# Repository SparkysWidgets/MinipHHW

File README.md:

Welcome To: MinipH Hardware Repo!!
================================

##### Note: This is for the MinipH Hardware Version 4 Branch

MinipH Hardware Design Files in EAGLE. Not much to say, there are some custom parts will add Library after I clean it up!

Schematic Info
-------------------------
##### Basic schematic is split into sections
- Analog Front End - pH gain and offset stages
- 12bit ADC
- VREF
- VGND generated by Op-amp, probe is biased
- Reverse V protection pFET

Board Layout Info
-------------------------
##### Form factor is consistent with all other mini interface boards

- Standard 2.54mm pitch header and Grove style connector
- Guard ring on pH input stage, care must be taken in layout here
- Added back in solder bridge jumper to select if Vref should be used or not (Its an expensive BurrBrown guy and really only needed for super sensitive use)

Errata
-------------------------

##### Just a quick list of current issues
- Mostly stable design older errata resolved, new may be created will be updated

Firmware
-------------------------

- Take a look in [MinipH's Firmware Repo](https://github.com/SparkysWidgets/MinipHBFW) For Arduino!
- Check out my USB pH interface[LeoPhi](https://www.sparkyswidgets.com/portfolio-item/leophi-usb-arduino-ph-sensor/) for a powerful and easy to use USB PH Probe interface!

Basic Usage
-------------------------

####See [MinipH's Firmware Repo](https://github.com/SparkysWidgets/MinipHBFW)

License Info
-------------------------

<p>This is a fully open source project released under the CC BY license</p>
<br />
<span xmlns:dct="http://purl.org/dc/terms/" property="dct:title">MinipH</span> by <a xmlns:cc="http://creativecommons.org/ns#" href="www.sparkyswidgets.com" property="cc:attributionName" rel="cc:attributionURL">Ryan Edwards, Sparky's Widgets</a> is licensed under a <a rel="license" href="http://creativecommons.org/licenses/by-sa/3.0/deed.en_US">Creative Commons Attribution-ShareAlike 3.0 Unported License</a>.<br />
Based on a work at <a xmlns:dct="http://purl.org/dc/terms/" href="/portfolio-item/leophi-usb-arduino-ph-sensor/" rel="dct:source">http://www.sparkyswidgets.com/portfolio-item/miniph-i2c-ph-interface/</a>

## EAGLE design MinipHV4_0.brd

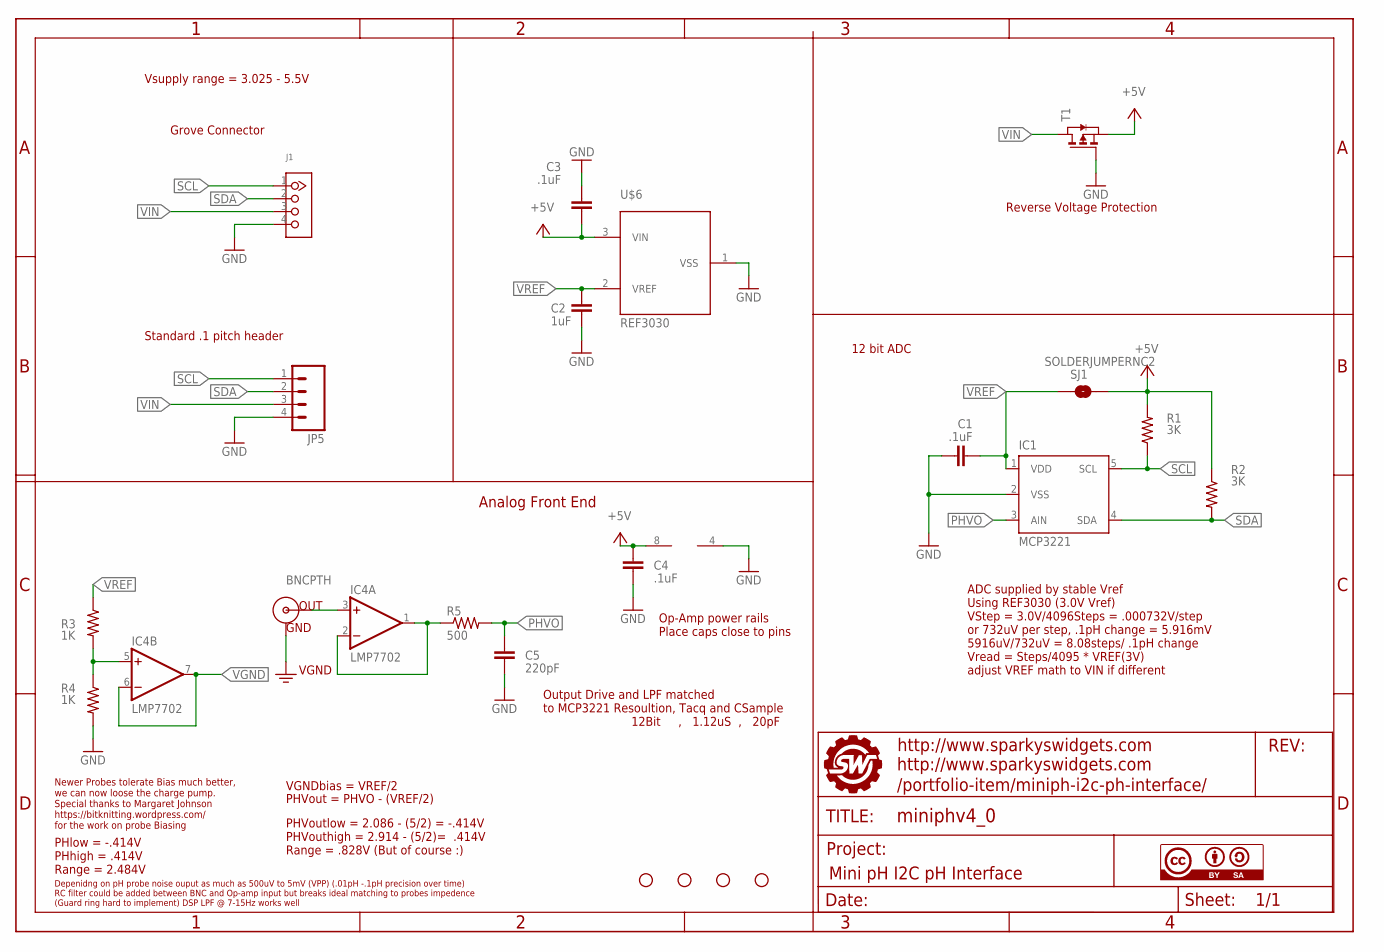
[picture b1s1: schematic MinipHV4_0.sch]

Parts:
C1, C3, C4: .1uF; 0805
C2: 1uF; 0805
C5: 220pF; 0805
IC1: MCP3221; SOT23-DBV
IC4: LMP7702; SO08
J1: TWIG-4P-2.0-2.0; 4P-2.0
JP1, JP2, JP3, JP4: STAND-OFF
JP5: M04PTH; 1X04
R1, R2: 3K; 0805
R3, R4: 1K; 0805
R5: 500; 0805
SJ1: SOLDERJUMPERNC2; SJ_2S-NOTRACE
T1: PMOSSOT23; SOT-23
U$2: BNCPTH; BNC
U$4: FRAME_MINIPH; SWPCBLOGOWITHINFO
U$5: CC-BY-SA
U$6: REF3030; SOT-23

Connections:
+5V: C3.1, C4.1, IC4.8 (V+), R1.2, R2.1, SJ1.2, T1.2 (S), U$6.3 (VIN)
GND: C1.1, C2.2, C3.2, C4.2, C5.2, IC1.2 (VSS), IC4.4 (V-), J1.4, JP5.4, R4.2, T1.3 (G), U$6.1 (VSS)
unnamed: IC4.5 (+IN), R3.2, R4.1
unnamed: IC4.1 (OUT), IC4.2 (-IN), R5.1
PHVIN: IC4.3 (+IN), U$2.S (OUT)
PHVO: C5.1, IC1.3 (AIN), R5.2
SCL: IC1.5 (SCL), J1.1, JP5.1, R1.1
SDA: IC1.4 (SDA), J1.2, JP5.2, R2.2
VGND: IC4.6 (-IN), IC4.7 (OUT), U$2.GND
VIN: J1.3, JP5.3, T1.1 (D)
VREF: C1.2, C2.1, IC1.1 (VDD), R3.1, SJ1.1, U$6.2 (VREF)

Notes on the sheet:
Grove Connector
Standard .1 pitch header
12 bit ADC
Analog Front End
Op-Amp power rails Place caps close to pins
Depenidng on pH probe noise ouput as much as 500uV to 5mV (VPP) (.01pH -.1pH precision over time) RC filter could be added between BNC and Op-amp input but breaks ideal matching to probes impedence (Guard ring hard to implement) DSP LPF @ 7-15Hz works well
Newer Probes tolerate Bias much better, we can now loose the charge pump. Special thanks to Margaret Johnson https://bitknitting.wordpress.com/ for the work on probe Biasing
VGNDbias = VREF/2
PHVout = PHVO - (VREF/2)
PHlow = -.414V PHhigh = .414V Range = 2.484V
PHVoutlow = 2.086 - (5/2) = -.414V PHVouthigh = 2.914 - (5/2)= .414V Range = .828V (But of course :)
Output Drive and LPF matched to MCP3221 Resoultion, Tacq and CSample 12Bit , 1.12uS , 20pF
Vsupply range = 3.025 - 5.5V
ADC supplied by stable Vref Using REF3030 (3.0V Vref) VStep = 3.0V/4096Steps = .000732V/step or 732uV per step, .1pH change = 5.916mV 5916uV/732uV = 8.08steps/ .1pH change Vread = Steps/4095 * VREF(3V) adjust VREF math to VIN if different
Reverse Voltage Protection

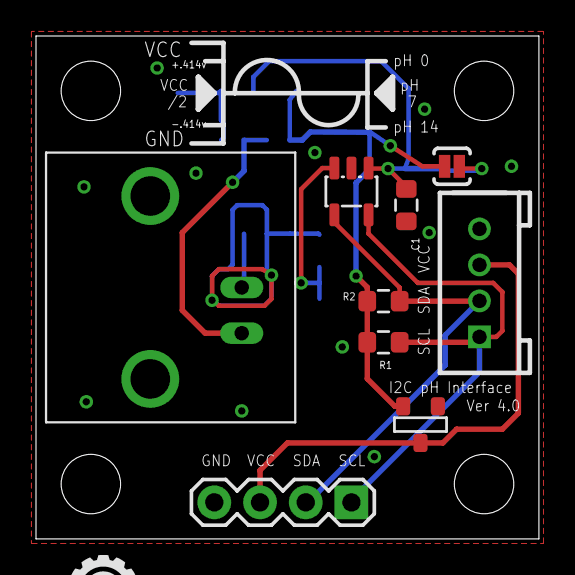
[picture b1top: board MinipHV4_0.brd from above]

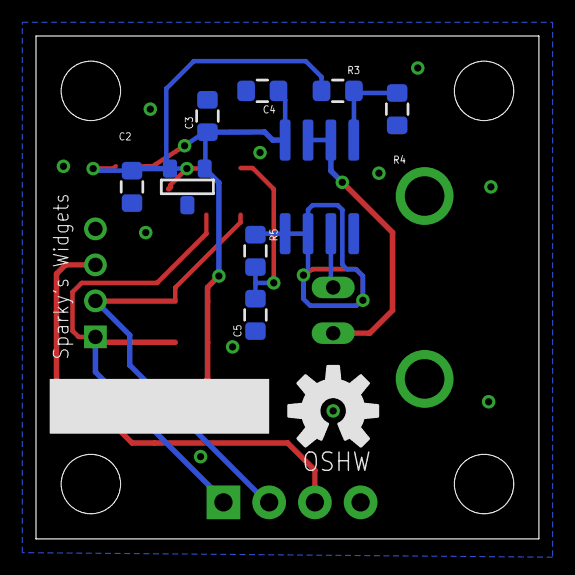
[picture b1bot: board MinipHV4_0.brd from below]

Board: 2 copper layers, 27.9 x 27.9 mm, 27 parts (10 on the bottom side), 11 nets.

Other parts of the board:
U$1, U$7: SILK_ARROW
U$3: OSHW-LOGO-M

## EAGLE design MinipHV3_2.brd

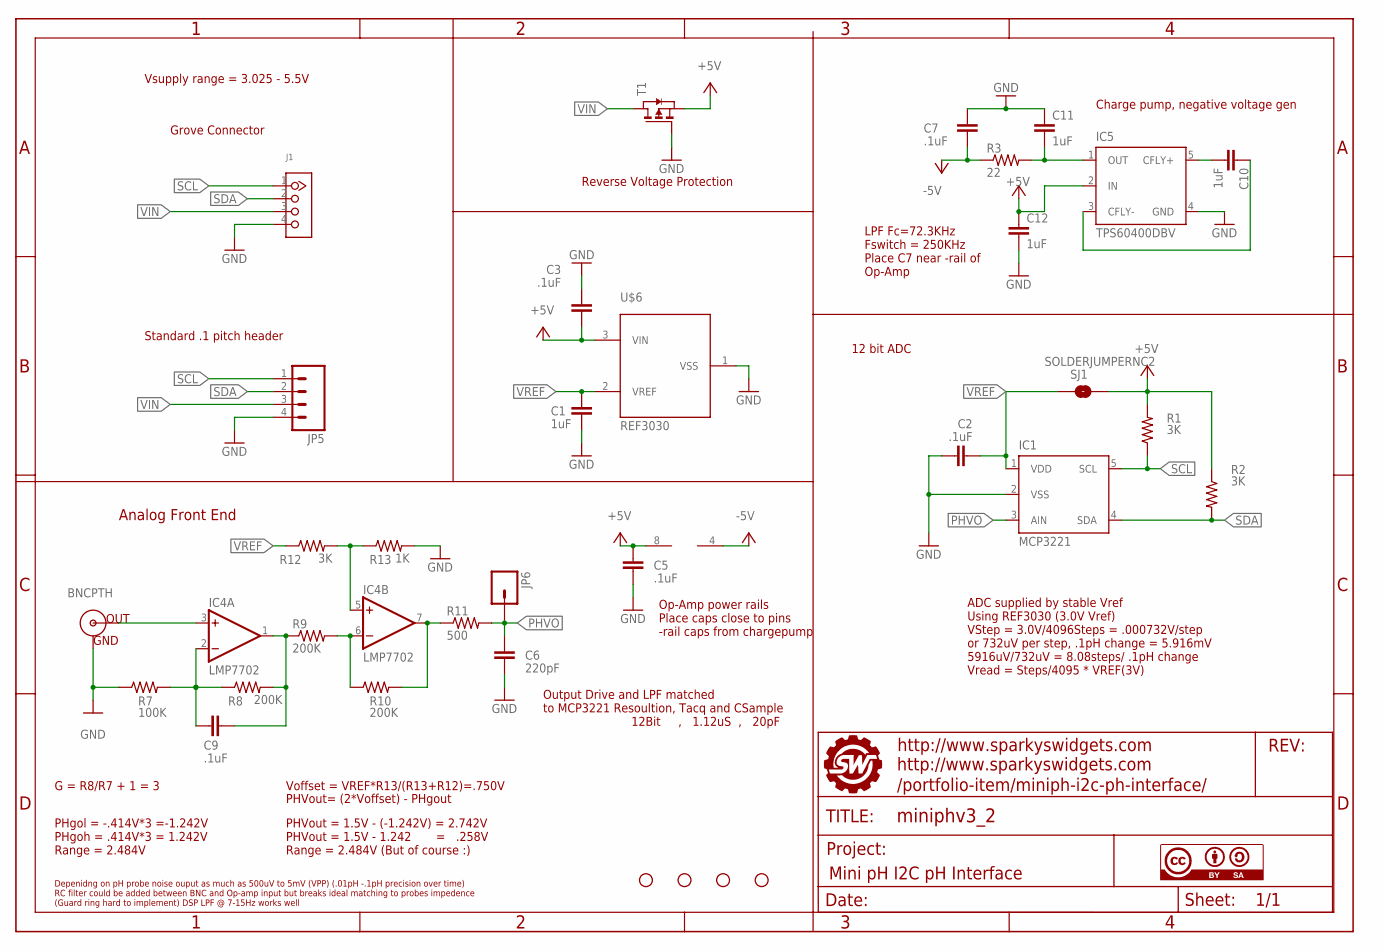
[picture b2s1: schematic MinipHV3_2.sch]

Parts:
C1, C10, C11, C12: 1uF; 0805
C2, C3, C5, C7, C9: .1uF; 0805
C6: 220pF; 0805
IC1: MCP3221; SOT23-DBV
IC4: LMP7702; SO08
IC5: TPS60400DBV; SOT23-DBV
J1: TWIG-4P-2.0-2.0; 4P-2.0
JP1, JP2, JP3, JP4: STAND-OFF
JP5: M04PTH; 1X04
JP6: M01PTH; 1X01
R1, R2, R12: 3K; 0805
R3: 22; 0805
R7: 100K; 0805
R8, R9, R10: 200K; 0805
R11: 500; 0805
R13: 1K; 0805
SJ1: SOLDERJUMPERNC2; SJ_2S-NOTRACE
T1: PMOSSOT23; SOT-23
U$2: BNCPTH; BNC
U$4: FRAME_MINIPH; SWPCBLOGOWITHINFO
U$5: CC-BY-SA
U$6: REF3030; SOT-23

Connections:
+5V: C3.1, C5.1, C12.1, IC4.8 (V+), IC5.2 (IN), R1.2, R2.1, SJ1.2, T1.2 (S), U$6.3 (VIN)
-5V: C7.2, IC4.4 (V-), R3.1
GND: C1.2, C2.1, C3.2, C5.2, C6.2, C7.1, C11.1, C12.2, IC1.2 (VSS), IC5.4 (GND), J1.4, JP5.4, R7.1, R13.2, T1.3 (G), U$2.GND, U$6.1 (VSS)
unnamed: IC4.5 (+IN), R12.2, R13.1
unnamed: IC4.7 (OUT), R10.2, R11.1
unnamed: IC4.6 (-IN), R9.2, R10.1
unnamed: C11.2, IC5.1 (OUT), R3.2
unnamed: C9.2, IC4.2 (-IN), R7.2, R8.1
unnamed: IC4.3 (+IN), U$2.S (OUT)
unnamed: C9.1, IC4.1 (OUT), R8.2, R9.1
unnamed: C10.1, IC5.3 (CFLY-)
unnamed: C10.2, IC5.5 (CFLY+)
PHVO: C6.1, IC1.3 (AIN), JP6.1, R11.2
SCL: IC1.5 (SCL), J1.1, JP5.1, R1.1
SDA: IC1.4 (SDA), J1.2, JP5.2, R2.2
VIN: J1.3, JP5.3, T1.1 (D)
VREF: C1.1, C2.2, IC1.1 (VDD), R12.1, SJ1.1, U$6.2 (VREF)

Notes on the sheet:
Grove Connector
Standard .1 pitch header
12 bit ADC
Charge pump, negative voltage gen
Analog Front End
Op-Amp power rails Place caps close to pins -rail caps from chargepump
Depenidng on pH probe noise ouput as much as 500uV to 5mV (VPP) (.01pH -.1pH precision over time) RC filter could be added between BNC and Op-amp input but breaks ideal matching to probes impedence (Guard ring hard to implement) DSP LPF @ 7-15Hz works well
G = R8/R7 + 1 = 3
Voffset = VREF*R13/(R13+R12)=.750V
PHVout= (2*Voffset) - PHgout
PHgol = -.414V*3 =-1.242V PHgoh = .414V*3 = 1.242V Range = 2.484V
PHVout = 1.5V - (-1.242V) = 2.742V PHVout = 1.5V - 1.242 = .258V Range = 2.484V (But of course :)
Output Drive and LPF matched to MCP3221 Resoultion, Tacq and CSample 12Bit , 1.12uS , 20pF
Vsupply range = 3.025 - 5.5V
LPF Fc=72.3KHz Fswitch = 250KHz Place C7 near -rail of Op-Amp
ADC supplied by stable Vref Using REF3030 (3.0V Vref) VStep = 3.0V/4096Steps = .000732V/step or 732uV per step, .1pH change = 5.916mV 5916uV/732uV = 8.08steps/ .1pH change Vread = Steps/4095 * VREF(3V)
Reverse Voltage Protection

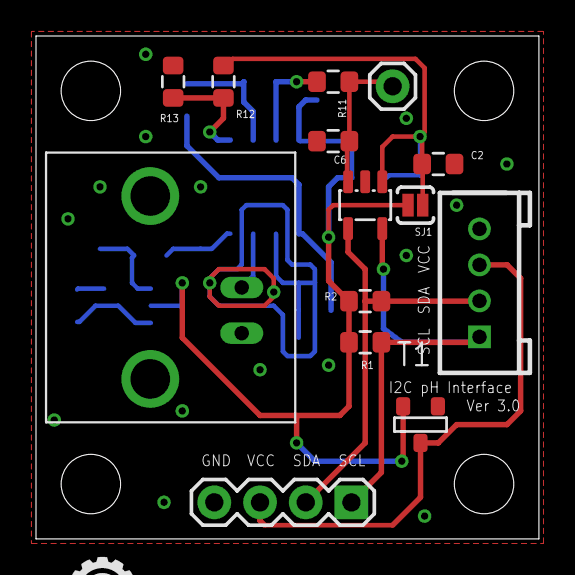
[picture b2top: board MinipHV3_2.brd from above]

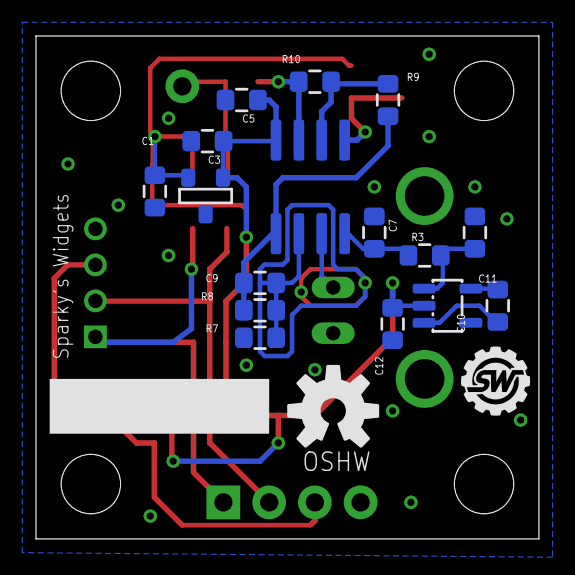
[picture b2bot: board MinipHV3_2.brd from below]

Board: 2 copper layers, 27.9 x 27.9 mm, 38 parts (18 on the bottom side), 17 nets.

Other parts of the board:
U$1: SWPCBLOGO
U$3: OSHW-LOGO-M

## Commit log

2013-04-23 Added Design Files
2013-04-23 updated design files to v2_1
2013-06-04 updated schematic
2014-09-26 Cleaned up design a bit, added changed to readme
2014-09-26 Updated Project URL in README
2014-09-26 added in bridge jumper VCC to Vref
2015-01-19 Added sch in pdf form and skethup 3d model
2015-10-06 Updated to version 4.0

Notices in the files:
parts and their libraries:
SparkFun-Aesthetics: Licensing: CC v3.0 Share-Alike You are welcome to use this library for commercial purposes.
